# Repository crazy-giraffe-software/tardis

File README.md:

# Tardis

So Quirky G and I are driving down the road with the kids in the back, just chatting about stuff.  On this particular day, we were discussing getting a new vehicle:

&nbsp;&nbsp;_QG: I'd really like to get a new car._  
&nbsp;&nbsp;_S: What are you thinking about?_  
&nbsp;&nbsp;_QG: A highlander but I don't think we should spend the money right now._  
&nbsp;&nbsp;_S: You don't you like this van?_  
&nbsp;&nbsp;_QG: I hate it!_  
&nbsp;&nbsp;_S: Well, it's TARDIS blue._  
&nbsp;&nbsp;_QG: I'd totally drive it if it looked like a TARDIS!_  
&nbsp;&nbsp;_S: Does it need to have a flashing lighting and make that sound?_  
&nbsp;&nbsp;_QC: Why wouldn't it?_  
&nbsp;&nbsp;_S: I can do that._  

And so this project was born: Make the van look like a TARDIS.

Want to read [more](http://crazygiraffesoftware.net/2019/06/02/tardis-van/)?

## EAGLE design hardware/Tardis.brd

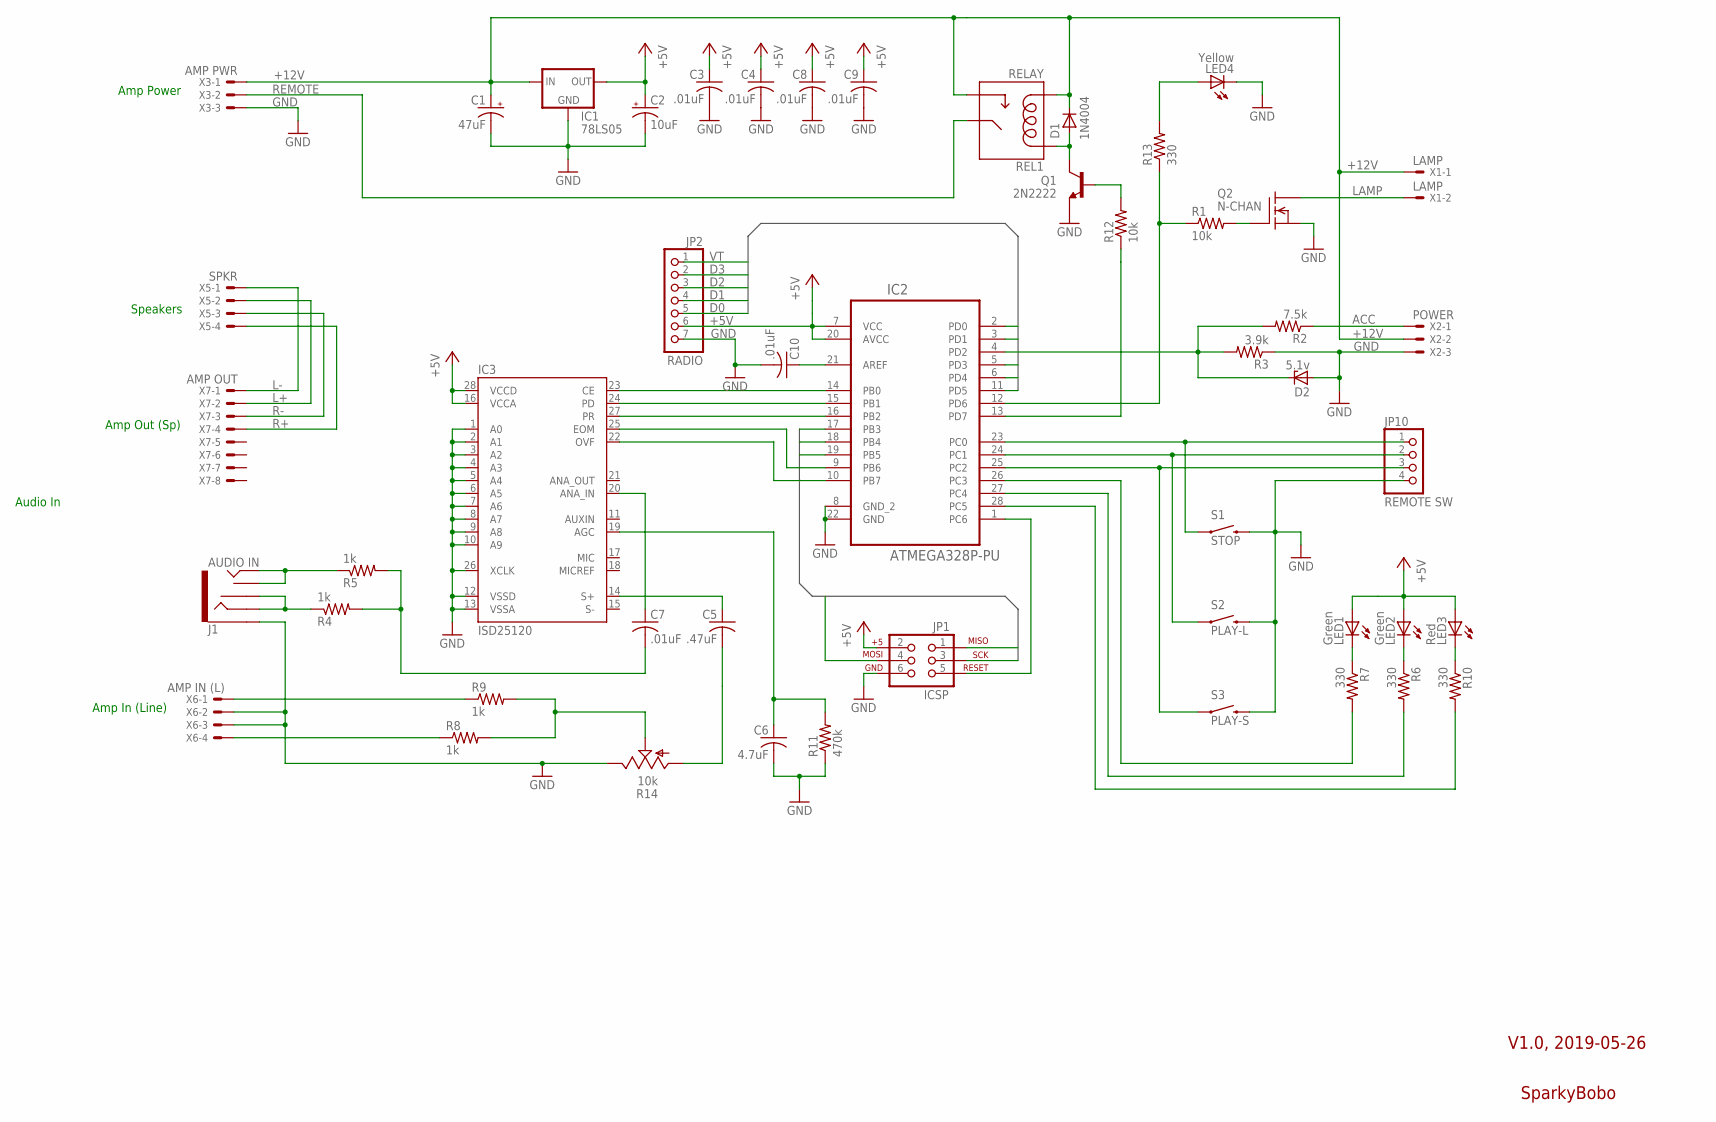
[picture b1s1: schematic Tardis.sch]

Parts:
C1: 47uF; E3,5-8
C2: 10uF; E3,5-8
C3, C4, C8, C9, C10: .01uF; C025-025X050
C5: .47uF; C025-025X050
C6: 4.7uF; C025-025X050
C7: .01uF; C050-025X075
D1: 1N4004; DIODE-1N4148
D2: 5.1v; DO35Z10
IC1: 78LS05; TO-92
IC2: ATMEGA328P-PU; DIP254P762X457-28
IC3: ISD25120; CRAZYGIRAFFE_DIL28-6
J1: AUDIO IN; AUDIO-JACK
JP1: ICSP; 2X3
JP2: RADIO; 1X07
JP10: REMOTE SW; 1X04
LED1, LED2: Green; LED5MM
LED3: Red; LED5MM
LED4: Yellow; LED5MM
Q1: 2N2222; TO-92
Q2: N-CHAN; TO220
R1, R12: 10k; 0207/10
R2: 7.5k; 0207/10
R3: 3.9k; 0207/10
R4, R5, R8, R9: 1k; 0207/10
R6, R7, R10, R13: 330; 0207/10
R11: 470k; 0207/10
R14: 10k; CA6V
REL1: RELAY; CRAZYGIRAFFE_RELAY-DIP
S1: STOP; CRAZYGIRAFFE_TACTILE-PTH-12MM
S2: PLAY-L; CRAZYGIRAFFE_TACTILE-PTH-12MM
S3: PLAY-S; CRAZYGIRAFFE_TACTILE-PTH-12MM
X1: LAMP; KK-156-2
X2: POWER; KK-156-3
X3: AMP PWR; KK-156-3
X5: SPKR; KK-156-4
X6: AMP IN (L); KK-156-4
X7: AMP OUT; KK-156-8

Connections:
+5V: C2.+, C3.1, C4.1, C8.1, C9.1, IC1.3 (OUT), IC2.7 (VCC), IC2.20 (AVCC), IC3.16 (VCCA), IC3.28 (VCCD), JP1.2, JP2.6, LED1.A, LED2.A, LED3.A
+12V: C1.+, D1.C, IC1.2 (IN), REL1.2 (COIL2), REL1.4 (NO), X1.1, X2.2, X3.1
ACC: R2.1, X2.1
AUD-OUT: R8.2, R9.2, R14.S
D0: IC2.3 (PD1), JP2.5
D1: IC2.2 (PD0), JP2.4
D2: IC2.11 (PD5), JP2.3
D3: IC2.6 (PD4), JP2.2
GND: C1.-, C2.-, C3.2, C4.2, C6.2, C8.2, C9.2, C10.2, D2.A, IC1.1 (GND), IC2.8 (GND_2), IC2.22 (GND), IC3.1 (A0), IC3.2 (A1), IC3.3 (A2), IC3.4 (A3), IC3.5 (A4), IC3.6 (A5), IC3.7 (A6), IC3.8 (A7), IC3.9 (A8), IC3.10 (A9), IC3.12 (VSSD), IC3.13 (VSSA), IC3.26 (XCLK), J1.SLEEVE, JP1.6, JP2.7, JP10.4, LED4.K (C), Q1.1 (E), Q2.3 (S), R3.1, R11.1, R14.E, S1.3 (2), S2.3 (2), S3.3 (2), X2.3, X3.3, X6.2, X6.3
L+: X5.2, X7.2
L-: X5.1, X7.1
LAMP: Q2.2 (D), X1.2
MISO: IC2.18 (PB4), JP1.1
MOSI: IC2.17 (PB3), JP1.4
unnamed: Q2.1 (G), R1.2
unnamed: Q1.2 (B), R12.2
unnamed: IC2.13 (PD7), R12.1
unnamed: D2.C, IC2.4 (PD2), R2.2, R3.2
unnamed: IC2.16 (PB2), IC3.27 (PR)
unnamed: IC2.1 (PC6), JP1.5
unnamed: C5.1, IC3.14 (S+)
unnamed: IC2.23 (PC0), JP10.1, S1.1
unnamed: C6.1, IC3.19 (AGC), R11.2
unnamed: C7.1, IC3.20 (ANA_IN)
unnamed: IC2.12 (PD6), R1.1, R13.1
unnamed: IC2.15 (PB1), IC3.24 (PD)
unnamed: IC2.14 (PB0), IC3.23 (CE)
unnamed: IC2.24 (PC1), JP10.2, S2.1
unnamed: J1.RING, J1.RSH, R4.1
unnamed: IC2.25 (PC2), JP10.3, S3.1
unnamed: IC2.26 (PC3), R7.2
unnamed: LED1.K (C), R7.1
unnamed: LED2.K (C), R6.1
unnamed: J1.TIP, J1.TSH, R5.1
unnamed: R9.1, X6.1
unnamed: R8.1, X6.4
unnamed: IC2.9 (PB6), IC3.25 (EOM)
unnamed: IC2.10 (PB7), IC3.22 (OVF)
unnamed: LED3.K (C), R10.1
unnamed: IC2.27 (PC4), R6.2
unnamed: LED4.A, R13.2
unnamed: C10.1, IC2.21 (AREF)
unnamed: D1.A, Q1.3 (C), REL1.1 (COIL1)
unnamed: C7.2, R4.2, R5.2
unnamed: C5.2, R14.A
R+: X5.4, X7.4
R-: X5.3, X7.3
REMOTE: REL1.3 (MAIN), X3.2
SCK: IC2.19 (PB5), JP1.3
ST1: IC2.28 (PC5), R10.2
VT: IC2.5 (PD3), JP2.1

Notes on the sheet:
Speakers
Amp Out (Sp)
Amp Power
Amp In (Line)
Audio In
V1.0, 2019-05-26
SparkyBobo

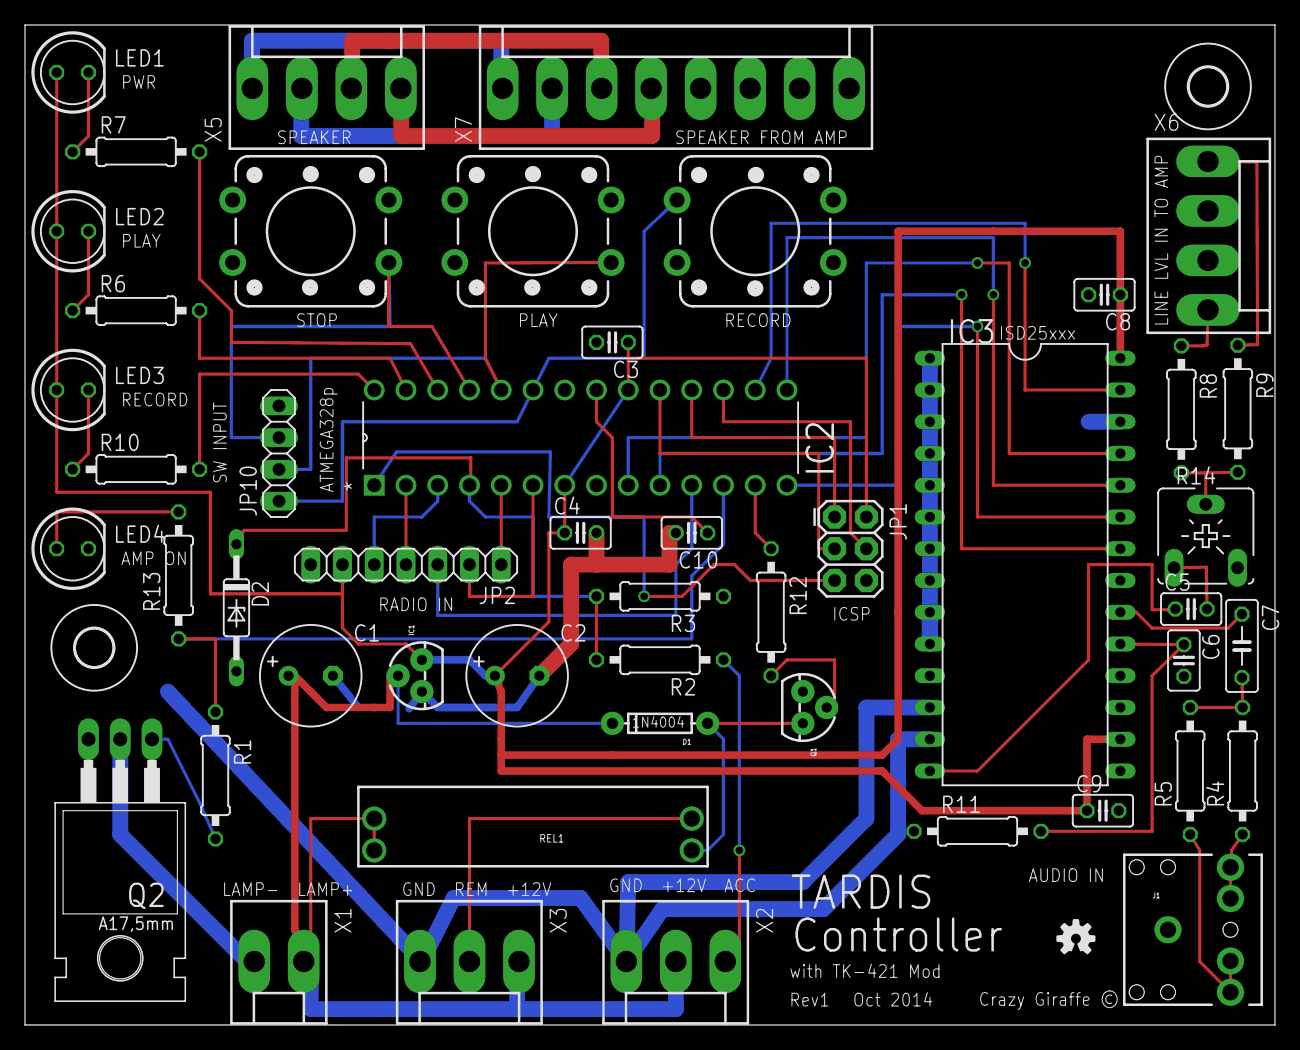
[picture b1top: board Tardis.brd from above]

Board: 2 copper layers, 100.0 x 80.0 mm, 52 parts (0 on the bottom side), 51 nets.

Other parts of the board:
U$1, U$2: 3,0
U$3: OSHW-LOGO-S

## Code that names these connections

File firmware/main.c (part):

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// Chip:
// ATMega328
//
// PB0:        ISD25xxx CE (Chip Enable)
// PB1:        ISD25xxx PD (Power Down)
// SS/PB2:     ISD25xxx PR (Play/Record)
// MOSI/PB3:   MOSI for ICSP
// MISO/PB4:   MISO for ICSP
// SCLK/PB5:   SCLK for ICSP
// XTAL1/PB6:  ISD25xxx OEM (End of mesaage)
// XTAL2/PB7:  ISD25xxx OVF (Overflow)
// ...
// PC0:        Start Sw
// PC1:        Stop Sw
// PC2:        Record Sw
// PC3:        Led 1
// SDA/PC4:    Led 2
// SCL/PC5:    Led 3
// RST/PC6:    Reset
// ...
// RXD/PD0:    D1 from radio
// TXD/PD1:    D0 from radio
// PD2/INT0:   Acc from vehicle
// PD3/INT1:   VT from radio
// PD4:        D3 from radio
// PD5:        D2 from radio
// PD6:        Lamp
// PD7:        Amp Remote

//
// Configuration
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
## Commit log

2019-05-27 Add firmware and hardware files.
2019-05-27 Add custom library.

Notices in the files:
firmware/main.c:
Copyright (c) 2019 crazy-giraffe-software
MIT License
parts and their libraries:
SparkFun-Connectors: Licensing: CC v3.0 Share-Alike You are welcome to use this library for commercial purposes.
SparkFun-Aesthetics: Licensing: Creative Commons ShareAlike 4.0 International - https://creativecommons.org/licenses/by-sa/4.0
